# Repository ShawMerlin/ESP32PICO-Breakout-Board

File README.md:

# ESP32PICO-Breakout-Board

Here I have a simple breakout board for the new ESP32-PICO Chip.
All the parts I have included with JLCPCB Numbers so their assembly service can be used as well.

*Still getting some values on a few decoupling capacitors*

Pre-made Breakout boards for this are $30+ on sites so I wanted a cost effective option for testing this chip.
Feel free to take the Kicad files and change them however you see fit.  Enjoy!!

We want to update our ShawLED Controller board with this little chip, very exciting times!!
www.shawtechlighting.com

Features
* Full USB Integration
* A few breakout GPIO Pins (6)
* RX & TX USB Transfer LEDs
* Switch for hold in boot & reset
* 2 Antenna options (On Board and SMA)
* Switch for changing between the 2 Antenna's

3D Model of a Quarter was put in the picture to give an idea of how tiny this little guy is.  :)

I run a Facebook page for all my electronic/modding adventures.  I post things on there before they end up here on Github.
I love the feedback and comments that people share.  It helps us achieve bigger and better things!!

www.facebook.com/geekislandgaming

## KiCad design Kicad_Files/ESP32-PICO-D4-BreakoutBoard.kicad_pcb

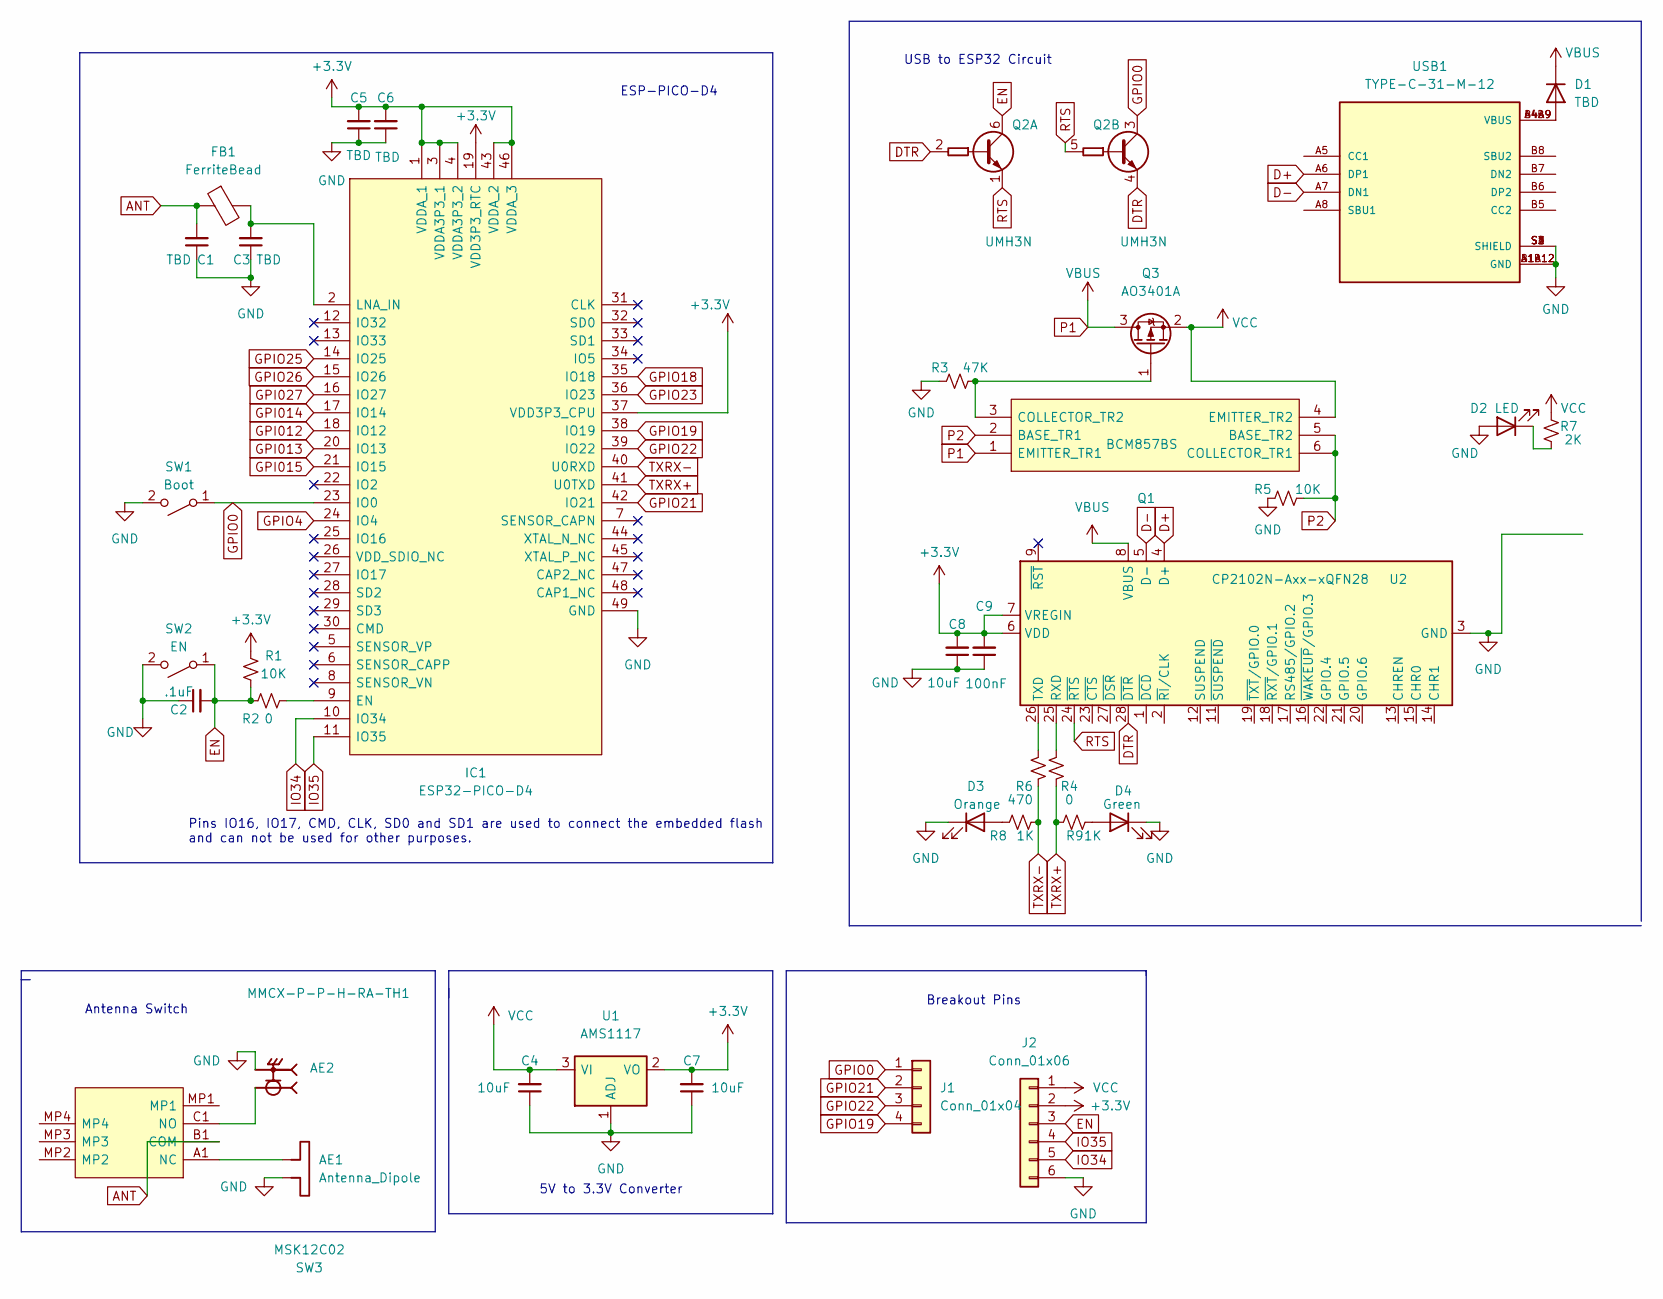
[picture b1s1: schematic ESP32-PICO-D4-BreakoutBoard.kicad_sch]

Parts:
AE1: Antenna_Dipole; Texas_SWRA117D_2.4GHz_Right
AE2: MMCX-P-P-H-RA-TH1; SAMTEC_MMCX-P-P-H-RA-TH1; PARTREV E
C1, C3, C5, C6: TBD; C_0603_1608Metric
C2: .1uF; C_0603_1608Metric
C4, C7, C8: 10uF; C_0603_1608Metric
C9: 100nF; C_0603_1608Metric
D1: TBD; DIODE_SOD2513X120N
D2: LED; LED_0603_1608Metric
D3: Orange; LED_0603_1608Metric
D4: Green; LED_0603_1608Metric
FB1: FerriteBead; R_1206_3216Metric
IC1: ESP32-PICO-D4; ESP32-PICO-D4-PQFN50P700X700X104-49N; Manufacturer_Part_Number ESP32-PICO-D4; Mouser Part Number 356-ESP32-PICO-D4
J1: Conn_01x04; PinSocket_1x04_P2.54mm_Vertical
J2: Conn_01x06; PinSocket_1x06_P2.54mm_Vertical
Q1: BCM857BS; BCM857BS_SOT65P210X110-6N; Manufacturer_Part_Number BCM857BS; Mouser Part Number N/A
Q2: UMH3N; SOT-363_SC-70-6
Q3: AO3401A; CJ2301_SOT95P240X115-3N
R1, R5: 10K; R_0603_1608Metric
R2, R6: 0; R_0603_1608Metric
R3: 47K; R_0603_1608Metric
R4: 470; R_0603_1608Metric
R7: 2K; R_0603_1608Metric
R8, R9: 1K; R_0603_1608Metric
SW1: Boot; Switch_SKRKAEE020
SW2: EN; Switch_SKRKAEE020
SW3: MSK12C02; Manufacturer_Part_Number MSK12C02
U1: AMS1117; SOT-223-3_TabPin2
U2: CP2102N-Axx-xQFN28; QFN-28-1EP_5x5mm_P0.5mm_EP3.35x3.35mm
USB1: TYPE-C-31-M-12; USBC_HRO_TYPE-C-31-M-12; PARTREV A

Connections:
+3V3: C5.2, C6.2, C7.2, C8.2, C9.2, IC1.1 (VDDA_1), IC1.3 (VDDA3P3_1), IC1.4 (VDDA3P3_2), IC1.19 (VDD3P3_RTC), IC1.37 (VDD3P3_CPU), IC1.43 (VDDA_2), IC1.46 (VDDA_3), J2.2, R1.2, U1.2 (VO), U2.6 (VDD), U2.7 (VREGIN)
ANT: C1.2, FB1.1, SW3.B1 (COM)
D+: U2.4 (D+), USB1.A6 (DP1)
D-: U2.5 (D-), USB1.A7 (DN1)
DTR: Q2.2 (B1), Q2.4 (E2), U2.28 (~DTR)
EN: C2.2, J2.3, Q2.6 (C1), R1.1, R2.1, SW2.1 (A)
GND: AE1.2, AE2.S1, AE2.S2, AE2.S3, AE2.S4, C1.1, C2.1, C3.1, C4.1, C5.1, C6.1, C7.1, C8.1, C9.1, D2.2 (A), D3.1 (K), D4.1 (K), IC1.49 (GND), J2.6, R3.1, R5.2, SW1.2 (B), SW2.2 (B), U1.1 (ADJ), U2.3 (GND), U2.29 (GND), USB1.A1B12 (GND), USB1.B1A12 (GND), USB1.S1 (SHIELD), USB1.S2 (SHIELD), USB1.S3 (SHIELD), USB1.S4 (SHIELD)
GPI012: IC1.18 (IO12)
GPI013: IC1.20 (IO13)
GPI014: IC1.17 (IO14)
GPI015: IC1.21 (IO15)
GPI027: IC1.16 (IO27)
GPIO0: IC1.23 (IO0), J1.1, Q2.3 (C2), SW1.1 (A)
GPIO4: IC1.24 (IO4)
GPIO18: IC1.35 (IO18)
GPIO19: IC1.38 (IO19), J1.4
GPIO21: IC1.42 (IO21), J1.2
GPIO22: IC1.39 (IO22), J1.3
GPIO23: IC1.36 (IO23)
GPIO25: IC1.14 (IO25)
GPIO26: IC1.15 (IO26)
IO34: IC1.10 (IO34), J2.5
IO35: IC1.11 (IO35), J2.4
unnamed: AE1.1, SW3.A1 (NC)
unnamed: C3.2, FB1.2, IC1.2 (LNA_IN)
unnamed: D1.2 (A), USB1.A4B9 (VBUS), USB1.B4A9 (VBUS)
unnamed: D2.1 (K), R7.2
unnamed: D3.2 (A), R8.1
unnamed: D4.2 (A), R9.2
unnamed: IC1.9 (EN), R2.2
unnamed: Q1.3 (COLLECTOR_TR2), Q3.1 (G), R3.2
unnamed: AE2.1, SW3.C1 (NO)
unnamed: R6.2, U2.25 (RXD)
unnamed: R4.2, U2.26 (TXD)
P1: D1.1 (K), Q1.1 (EMITTER_TR1), Q3.3 (D), U2.8 (VBUS)
P2: Q1.2 (BASE_TR1), Q1.5 (BASE_TR2), Q1.6 (COLLECTOR_TR1), R5.1
RTS: Q2.1 (E1), Q2.5 (B2), U2.24 (~RTS)
TXRX+: IC1.41 (U0TXD), R6.1, R9.1
TXRX-: IC1.40 (U0RXD), R4.1, R8.2
VCC: C4.2, J2.1, Q1.4 (EMITTER_TR2), Q3.2 (S), R7.1, U1.3 (VI)

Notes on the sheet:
Breakout Pins
USB to ESP32 Circuit
ESP-PICO-D4
Pins IO16, IO17, CMD, CLK, SD0 and SD1 are used to connect the embedded flash and can not be used for other purposes.
5V to 3.3V Converter
Antenna Switch

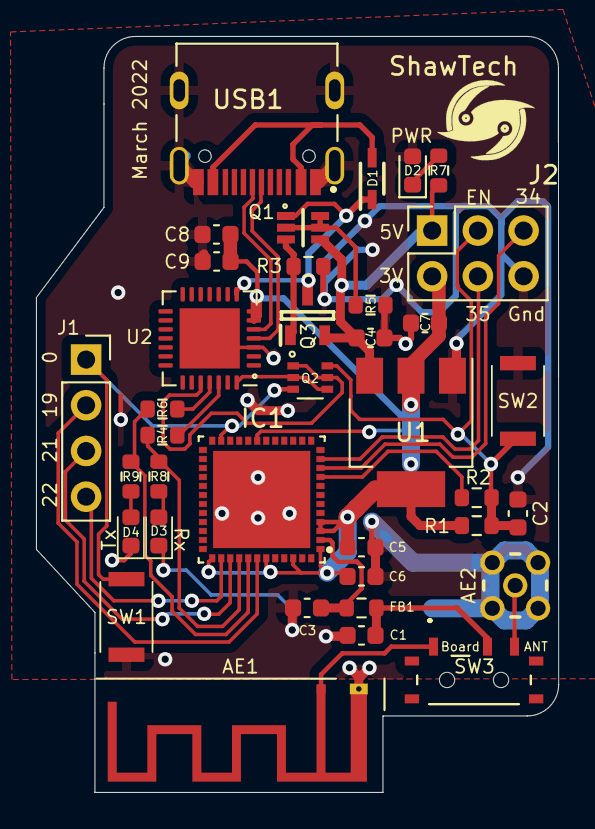
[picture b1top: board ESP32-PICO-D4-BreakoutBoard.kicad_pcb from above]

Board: 2 copper layers, 29.0 x 42.0 mm, 37 parts (0 on the bottom side), 30 nets.

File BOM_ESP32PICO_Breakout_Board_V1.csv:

Comment,Designator,Footprint,LCSC,Type
SMA Board Edge Bend ,AE2,ANT-TH_KH-SMA-K513-G,C411575,E
Boot Button - SKRKAEE020,"SW1,SW2",SW-SMD-2_2.9x3.9x1.7,C115357,E
ANT_Sel,SW3,SMD,C431540,E
Diode,D1,SOD-323,C124187,E
Power LED Blue,D2,LED_0603,C72041,B
Orange LED,D3,LED_0603,,
Green LED,D4,LED_0603,,
10k,"R1,R5",0603_Resistor,C25804,B
0R,"R2,R6",0603_Resistor,C21189,B
47K,R3,0603_Resistor,C25819,B
470R,R4,0603_Resistor,C23179,B
1.2K Resistor,"R7,R8,R9",0603_Resistor,C22765,B
BCM857BS,Q1,SOT65P210X110-6N,C105887,E
UMH3N,Q2,SMD:SOT-363,C62892,E
AO3401A,Q3,SOT95P240X115-3N,C15127,B
AMS1117,U1,SMD:SOT-223-3_TabPin2,C6186,B
CP2102,U2,QFN-28-1EP_5x5mm_P0.5mm_EP3.35x3.35mm,C6568,B
TYPE-C-31-M-12,USB1,TYPE-C-31_L8.94_W7.3,C165948,E
,C1,,,
,C3,,,
,C5,,,
,C6,,,
.1uF,"C2,C9",0603_Capacitor,C14663,B
10uF,"C4,C7,C8",0603_Capacitor,C96446,B
ESP32-PICO-D4,IC2,QFN-48_EP_7.0x7.0x0.5P,C193707,E
FerriteBead,FB1,R_1206_3216Metric,C1002,B
